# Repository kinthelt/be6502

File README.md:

# be6502
Notes on my Ben Eater 6502 build

## Description

I've been having fun building a 6502 breadboard computer based on Ben Eater's design (https://www.youtube.com/playlist?list=PLowKtXNTBypFbtuVMUVXNR0z1mu7dp7eH)

I made the decision early on to mostly follow along with the videos, but tweak the design a bit so that I would be forced to sit and think rather than just follow a recipe.  One of the major decisions was to use a 65C816S CPU rather than a 65C02S.  The extra 8 bits of address space (called banks) add new problems for me to solve if I am to use them.

On boot, the '816 behaves the same as the '02 as it operates in "emulation mode".  This simplifies things for me as I can treat the build the same as an '02 in bank 00.  If I want to access other banks, I need to store the data line bits in a latch on PHI2 low.  This is the start of where my design differs.

On PHI2 low, I store the data lines in a 74HC573 latch.  This is the bank byte, which I will use later.

The bank byte allows up to 255 banks of 64k each.  A whopping 16MB of address space is available to us.  That being said, I plan on only using a single 512kB RAM chip in my final design.  To start, I will use a single 8kB RAM chip.

With the addition of multiple banks, I won't be able to use a single 7400 to decode addresses without significant shadowing.  So the plan is to use an ATF22V10C programmable logic device to decode addresses.  The PLD allows me to remove some of the "wasted" space in Ben Eater's design.

## Schematic

The KiCad schematic is in [`kicad/`](kicad/), and [`kicad/be6502.pdf`](kicad/be6502.pdf)
is a plot of it. See [`kicad/README.md`](kicad/README.md).

There is also an unfabricated two-layer PCB layout made from the schematic,
[`kicad/be6502.kicad_pcb`](kicad/be6502.kicad_pcb). Renders are in
[`kicad/renders/`](kicad/renders/).

## The Ben Eater Address Space

| Range           | Size    | Device                          | Notes                                      |
|-----------------|---------|---------------------------------|--------------------------------------------|
| `$0000`–`$00FF` | 256 B   | RAM — zero page                 | 62256                                      |
| `$0100`–`$01FF` | 256 B   | RAM — stack                     | 62256                                      |
| `$0200`–`$3FFF` | 15.5 KB | RAM — general                   | 62256 (upper 16 KB of chip unusable)       |
| `$4000`–`$4FFF` | 4 KB    | unmapped                        |                                            |
| `$5000`         | 1 B     | 65C51 ACIA — data register      | read = RX, write = TX                      |
| `$5001`         | 1 B     | 65C51 ACIA — status / reset     | read = status, write = programmed reset    |
| `$5002`         | 1 B     | 65C51 ACIA — command register   |                                            |
| `$5003`         | 1 B     | 65C51 ACIA — control register   |                                            |
| `$5004`–`$5FFF` | ~4 KB   | ACIA register mirrors           | only A0–A1 decoded (RS0–RS1)               |
| `$6000`–`$600F` | 16 B    | 65C22 VIA — 16 registers        | RS0–RS3 = A0–A3                            |
| `$6010`–`$7FFF` | ~8 KB   | VIA register mirrors            | only A0–A3 decoded                         |
| `$8000`–`$FFFF` | 32 KB   | ROM                             | 28C256; vectors at `$FFFA`–`$FFFF`         |

### Address decode

| Device | Select logic |
|--------|--------------|
| ROM    | `/CE = NOT(A15)` |
| RAM    | `/CE = NOT(NOT(A15) AND Φ2)`, `/OE = A14` |
| VIA    | `/CS2 = NOT(NOT(A15) AND A14)`, `CS1 = A13` |
| ACIA   | `/CS1 = NOT(NOT(A15) AND A14 AND NOT(A13) AND A12)`, `CS0 = 1` |

**Quirks:** The 62256 is chip-enabled across `$0000`–`$7FFF`; only `/OE = A14` blocks reads above `$3FFF`. Writes to `$4000`–`$7FFF` still land in the RAM chip and cannot be read back, and writes in `$5000`–`$7FFF` hit RAM and the I/O device simultaneously.

## My Address Space

24-bit address space, notated `bank:offset`.

### Top level

| Range                 | Size   | Contents                                  |
|-----------------------|--------|-------------------------------------------|
| `$00:0000`–`$00:FFFF` | 64 KB  | Bank 0 — RAM, I/O, ROM (see below)        |
| `$01:0000`–`$07:FFFF` | 448 KB | RAM, full banks                           |
| `$08:0000`–`$7F:FFFF` | —      | Aliases of banks `$00`–`$07`              |
| `$80:0000`–`$80:7FFF` | 32 KB  | Video RAM (62256), future, not fitted     |
| `$80:8000`–`$FF:FFFF` | —      | Aliases of `$80:0000`–`$80:7FFF`          |

The GAL already decodes `/VRAMCE` for the video bank, but no video RAM is fitted yet.
GAL pin 17 is unconnected.

RAM total: 472 KB reachable of 512 KB installed (AS6C4008). The 40 KB shortfall is
bank 0's I/O window and ROM window shadowing the SRAM.

### Bank 0

| Range                 | Size    | Contents                                 |
|-----------------------|---------|------------------------------------------|
| `$00:0000`–`$00:00FF` | 256 B   | RAM — direct page (reset default)        |
| `$00:0100`–`$00:01FF` | 256 B   | RAM — stack (reset default)              |
| `$00:0200`–`$00:5FFF` | 23.5 KB | RAM — general                            |
| `$00:6000`–`$00:7FFF` | 8 KB    | I/O window — 74HC138, 8 × 1 KB slots     |
| `$00:8000`–`$00:FFFF` | 32 KB   | ROM (AT28C256)                           |

Direct page and stack are shown at their reset defaults. In native mode both are
relocatable anywhere within bank 0.

### I/O window

74HC138 enabled by `/IO_SELECT` from the GAL, selects driven by A10–A12.

| Output | Range                 | Device       | Registers                          |
|--------|-----------------------|--------------|------------------------------------|
| Y0     | `$00:6000`–`$00:63FF` | W65C22 VIA   | `$6000`–`$600F`, mirrored (A0–A3)  |
| Y1     | `$00:6400`–`$00:67FF` | unallocated  |                                    |
| Y2     | `$00:6800`–`$00:6BFF` | unallocated  |                                    |
| Y3     | `$00:6C00`–`$00:6FFF` | unallocated  |                                    |
| Y4     | `$00:7000`–`$00:73FF` | W65C51N ACIA | `$7000`–`$7003`, mirrored (A0–A1)  |
| Y5     | `$00:7400`–`$00:77FF` | unallocated  |                                    |
| Y6     | `$00:7800`–`$00:7BFF` | unallocated  |                                    |
| Y7     | `$00:7C00`–`$00:7FFF` | unallocated  |                                    |

### Vectors

| Range                 | Mode      |
|-----------------------|-----------|
| `$00:FFE4`–`$00:FFEF` | Native    |
| `$00:FFF8`–`$00:FFFF` | Emulation |

Both sets are in ROM. ROM is fixed at `$00:8000` — no vector remap or bank switching.

### Decode

Bank byte A16–A23 is captured from D0–D7 by a 74HC573, LE driven by `/PHI2`.

GAL (ATF22V10C) inputs: A12–A15, A16–A18, A23, PHI2, RWB.
A19–A22 are deliberately left as don't-cares — hence the aliasing above. Tighten
this first if a second RAM or VRAM device is ever added.

A16–A18 feed the SRAM address pins directly; the GAL uses them only to identify
bank 0. A23 alone separates the RAM banks from the video bank.

`/WE_RAM` is gated `PHI2 AND /RWB`. Raw RWB would write during PHI2 low, when the
data bus still carries the bank byte.

# Pinout Reference — 75HC138 and W65C22

For the 65C816 breadboard build. I/O window `$00:6000–$00:7FFF`,
enabled by IOSEL from the ATF22V10C (816DEC01).

---

## 74HC138 — 3-to-8 Line Decoder, DIP-16

| Pin | Name | Connect to |
|----:|------|------------|
| 1 | A | A10 |
| 2 | B | A11 |
| 3 | C | A12 |
| 4 | /E1 (/G2A) | IOSEL, GAL pin 20 |
| 5 | /E2 (/G2B) | GND — reserved PHI2 hook |
| 6 | E3 (G1) | VCC |
| 7 | Y7 | $7C00 slot |
| 8 | GND | GND |
| 9 | Y6 | $7800 slot |
| 10 | Y5 | $7400 slot |
| 11 | Y4 | $7000 — ACIA |
| 12 | Y3 | $6C00 slot |
| 13 | Y2 | $6800 slot |
| 14 | Y1 | $6400 slot |
| 15 | Y0 | $6000 — VIA CS2B |
| 16 | VCC | +5V |

100 nF from pin 16 to pin 8, close to the package, is the usual
recommendation. This build has no per-chip decoupling (no room). The
only decoupling capacitor is a 0.1 µF electrolytic across +5V and GND
at the bench supply connection.

### Output behaviour

All eight outputs idle **high**. Exactly one goes low at a time, and
only when every enable is satisfied. Nothing is selected at rest.

| Condition | Outputs |
|-----------|---------|
| Any enable unsatisfied | all eight high |
| Enabled, CBA = 000 | Y0 low, rest high |
| Enabled, CBA = 100 | Y4 low, rest high |

### Enables

Mixed polarity. All three must be true at once:

- pin 4 — LOW
- pin 5 — LOW
- pin 6 — HIGH

Naming varies by manufacturer. TI uses /G2A, /G2B, G1; others use
/E1, /E2, E3. Same pins, same behaviour, different letters. A
schematic found online may not match the datasheet in hand.

Pin 6 is the trap — the only active-high enable, sitting next to the
two active-low ones. Tied low, the part has no outputs at all and no
obvious reason why.

### Slot mapping

C:B:A = A12:A11:A10, straight through.

| Output | Address range | Device |
|--------|---------------|--------|
| Y0 | $00:6000–$00:63FF | W65C22 VIA |
| Y1 | $00:6400–$00:67FF | unallocated |
| Y2 | $00:6800–$00:6BFF | unallocated |
| Y3 | $00:6C00–$00:6FFF | unallocated |
| Y4 | $00:7000–$00:73FF | W65C51N ACIA |
| Y5 | $00:7400–$00:77FF | unallocated |
| Y6 | $00:7800–$00:7BFF | unallocated |
| Y7 | $00:7C00–$00:7FFF | unallocated |

Unused outputs are totem-pole, not open-drain — nothing to pull.
Leave open, or run to a header row while breadboarding.

---

## W65C22 VIA — DIP-40

| Pin | Signal | Connect to |
|----:|--------|------------|
| 1 | VSS | GND |
| 2–9 | PA0–PA7 | peripheral, ascending |
| 10–17 | PB0–PB7 | peripheral, ascending |
| 18 | CB1 | peripheral / shift clock |
| 19 | CB2 | peripheral / serial data |
| 20 | VDD | +5V |
| 21 | IRQB | CPU IRQB — see note |
| 22 | RWB | CPU RWB |
| 23 | CS2B | 74HC138 Y0, pin 15 |
| 24 | CS1 | VCC |
| 25 | PHI2 | system PHI2 |
| 26–33 | D7–D0 | data bus, **descending** |
| 34 | RESB | system reset |
| 35–38 | RS3–RS0 | A3–A0, **descending** |
| 39 | CA2 | peripheral |
| 40 | CA1 | peripheral |

### Chip select

To access a register: CS1 = logic 1 AND CS2B = logic 0.

CS1 is the tie-high enable, not the main select. WDC's default for
unused pins says the same thing from the other side — hold CS1 high,
hold CS2B low.

Y0 is active low, so it must land on CS2B. Y0 on CS1 selects the chip
whenever the slot is *not* addressed, and the VIA fights RAM and ROM
on the data bus every cycle.

### Descending pin runs

Pin 26 = D7, pin 33 = D0.
Pin 35 = RS3, pin 38 = RS0.

Both numbered opposite to the PA and PB runs on the same package.
Reversing the data bus produces bit-mirrored reads and writes that
look like a dead chip.

### IRQB — check the part marking

| Variant | IRQB output | Wiring |
|---------|-------------|--------|
| W65C22N, older NMOS/CMOS | open drain, pull down only | wire-OR, one pullup on the common line |
| W65C22S | totem pole, drives both levels | logic OR gate, or a <0.5 V diode in series, forward biased when IRQB is low, plus a pullup |

The W65C22S IRQB was meant for logically ORing rather than wire ORing.
Tying an S variant directly to another driven IRQ line is a driver
fight.

With the ACIA on the same node, this decides the interrupt topology
for the whole system. Settle it before wiring either chip.

This build uses a **W65C22N6TPG-14** (open drain). Its IRQB is wired
directly to the shared IRQB line with the ACIA, with a single pull-up
and no diode.

### Processor interface timing — 5 V, 14 MHz

| Symbol | Parameter | Min |
|--------|-----------|-----|
| tACR / tACW | CSx, RSx, RWB setup | 10 ns |
| tCAR / tCAW | CSx, RSx, RWB hold from PHI2 rising | 10 ns |
| tDCW | data bus setup (write) | 10 ns |
| tCDR | data bus delay (read) | 20 ns max |

The 10 ns setup is what the decode chain must beat:

    74HC573 → ATF22V10C → 74HC138 → CS2B

all settled 10 ns before PHI2 rises.

### W65C22S-specific

- **No output current limiting.** The S variant can overdrive
  connected circuitry. The NMOS 6522 and W65C22N have series
  resistors built in. Add external resistors on PA/PB when driving
  LEDs or an HD44780.
- **Bus holding on every pin except PHI2.** A floating input holds
  its last state rather than drifting — so a disconnected jumper can
  look like a working connection until something changes it.

---

## Signal chain

Active low end to end:

    IOSEL low  →  '138 enabled  →  one Y low  →  CS2B low  →  VIA selected

No inverters anywhere in the path.

---

## Sources

- WDC W65C22 datasheet (W65C22N and W65C22S), Sept 13 2010
- Standard 6522 DIP-40 pin numbering, which the W65C22 follows

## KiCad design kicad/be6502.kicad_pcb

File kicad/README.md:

# KiCad schematic and PCB

Schematic for the W65C816S breadboard computer, as built, and a two-layer PCB
laid out from it. Open `be6502.kicad_pro` in KiCad 7 or newer. `be6502.pdf` is
a plot of all sheets.

## Sheets

| Sheet | Contents |
|-------|----------|
| `be6502.kicad_sch` | Root: sheet index, memory map |
| `cpu.kicad_sch` | U1 W65C816S, U2 74HC573 bank latch, U3 ATF22V10C (816DEC02), X1 12 MHz oscillator, reset |
| `memory.kicad_sch` | U4 AT28C256 ROM, U5 AS6C4008 RAM |
| `io.kicad_sch` | U6 74HC138, U7 W65C22N VIA with Port B LEDs, U8 W65C51N ACIA, X2 1.8432 MHz oscillator, U9 MAX232N, J2 DB9 |
| `power.kicad_sch` | J1 bench supply, C1 |

Sheets connect through global labels.

## Signal names

Active-low signals use KiCad's overbar notation in both net labels and pin
names: `~{IOSEL}`, `~{ROMCE}`, `~{RAMCE}`, `~{OEGATE}`, `~{WEGATE}`, `~{RES}`,
`~{IRQ}`, `R/~{W}`, and so on.

| Schematic | decode.pld | WDC datasheet |
|-----------|------------|---------------|
| `~{IOSEL}` | `/IOSEL` | — |
| `R/~{W}` | `RWB` | RWB |
| `~{RES}` | — | RESB |
| `~{IRQ}` | — | IRQB |
| `~{CS2}` (VIA) | — | CS2B |
| `~{CS1}` (ACIA) | — | CS1B |

KiCad stores `/` in a net name as `{slash}`, so the read/write net is
`R{slash}~{W}` in the files. It still displays as R/W with a bar over the W.

The project library `be6502.kicad_sym` contains every symbol the schematic
uses. The W65C816S, W65C22, W65C51N and the programmed ATF22V10C are drawn
from the WDC and Microchip pinouts. The other parts are copied from the stock
KiCad libraries, with pins such as `OE`, `Load` and `CE#` renamed to `~{OE}`,
`LE` and `~{CE}`.

## Wiring

**CPU (U1)**
- `~{ABORT}`, BE, RDY and `~{NMI}` are tied directly to +5V.
- VDA, VPA, `~{VP}`, `~{ML}`, E and MX are not connected.
- `~{RES}` has a pull-up (R1) and a push button (SW1) to GND.
- `~{IRQ}` has a pull-up (R2). It is shared by the VIA and the ACIA, both open drain, with no diode.

**Clock**
- X1 is a 12 MHz DIP-14 oscillator driving GAL pin 1 (CLK2). The GAL divides it to PHI2 = 6 MHz.
- X1 pin 1 is not connected.

**Bank latch and decode (U2, U3)**
- The GAL pins are exactly as in the `PIN ASSIGNMENT` section of `pld/decode.pld`.
- `~{VRAMCE}` (GAL pin 17) is not connected, because the video RAM is future expansion.
- GAL pins 11, 13, 15 and 16 are spare.
- On the 74HC573, `~{OE}` goes to GND and LE comes from GAL pin 14.
- Q0–Q2 drive A16–A18 and Q7 drives A23. Q3–Q6 are not connected.

**Memory (U4, U5)**
- The ROM and RAM share `~{OEGATE}`.
- `~{WEGATE}` goes only to the RAM's `~{WE}`. The ROM's `~{WE}` is tied high.

**I/O decoder (U6, 74HC138)**
- A/B/C = A10/A11/A12.
- `~{E0}` = `~{IOSEL}`, `~{E1}` = GND, E2 = +5V.
- Y0 goes to the VIA's `~{CS2}` and Y4 to the ACIA's `~{CS1}`. The other outputs are not connected.

**VIA (U7, W65C22N6TPG-14)**
- CS1 = +5V, RS0–RS3 = A0–A3.
- Port A, CA1, CA2, CB1 and CB2 are not connected.
- Each PBn drives an LED (D1–D8) and a resistor (R3–R10) to GND: PBn → LED → resistor → GND.

**ACIA (U8)**
- CS0 = +5V, RS0–RS1 = A0–A1.
- X2 is a 1.8432 MHz DIP-8 oscillator driving XTLI. X2 pin 1 (EN) is tied to +5V.
- XTLO, RxC and `~{DTR}` are not connected. `~{CTS}`, `~{DSR}` and `~{DCD}` are tied to GND.

**RS-232 (U9 MAX232N, J2 DB9 female)**
- ACIA TxD → T1IN → T1OUT → DB9 pin 2.
- DB9 pin 3 → R1IN → R1OUT → ACIA RxD.
- ACIA `~{RTS}` → T2IN → T2OUT → DB9 pin 8.
- DB9 pin 5 = GND. DB9 pins 1, 4, 6, 7 and 9 are not connected.
- R2IN and R2OUT are not connected.
- The charge-pump capacitors are 1 µF electrolytics: C2 across C1+/C1−, C3 across C2+/C2−, C4 from VS+ to GND, C5 from VS− to GND.

**Power**
- J1 represents the leads from the +5V bench supply.
- C1 (0.1 µF electrolytic) across +5V and GND at the supply connection is the only decoupling capacitor.

**Resistor values**
- R1–R10 are 1k, measured with a multimeter.

## PCB

`be6502.kicad_pcb` is a 175 × 125 mm two-layer, all through-hole board made
from the schematic. It shows what the computer would look like on a PCB. It
has not been fabricated.

- Bare-board renders: `renders/front.png` and `renders/back.png`.
- 0.2 mm signal tracks and 0.5 mm `VCC`/`GND` tracks (net class `Power`),
  0.2 mm clearance, 0.8/0.4 mm vias. Both layers have a `GND` pour.
- Footprints the schematic did not specify: R 0207 axial with 7.62 mm pitch,
  C 5 mm radial electrolytic, 3 mm LEDs, 6 mm tactile switch for SW1, a 2-pin
  5.08 mm screw terminal for J1 (bench supply), and a right-angle female DE-9
  for J2.
- H1–H4 are M3 mounting holes. They exist only on the board.
- The tracks came from a simple
  grid router in `pcb-tools/` (`build.py` places, `route.py` routes,
  `finish.py` pours and writes the DRC report, `compose.py` and `render.js`
  make the images).
- DRC with KiCad 7.0.11 reports 0 violations and 0 unconnected pads.

The board follows the schematic exactly, so C1 is the only decoupling
capacitor. A real board should have a 0.1 µF capacitor next to each chip's
power pins. Add them to the schematic first, then use *Update PCB from
Schematic*.

## Verification

The project was generated with KiCad 7.0 and checked with `kicad-cli sch
export netlist`. Every net matches the wiring above, and the only unconnected
pins are the ones marked no-connect. ERC has not been run, because
`kicad-cli` 7 has no ERC command. Run it in the GUI.

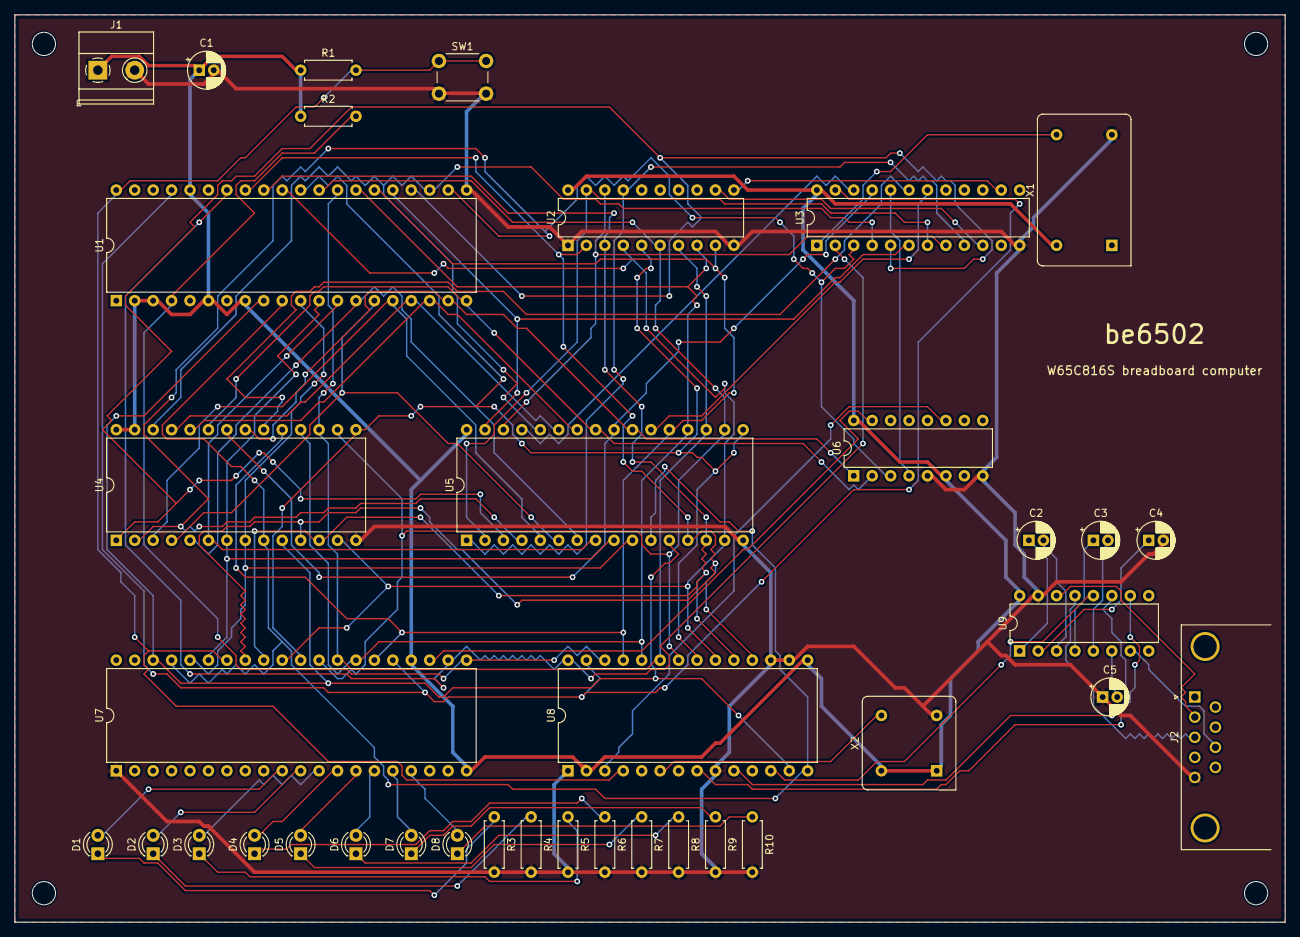
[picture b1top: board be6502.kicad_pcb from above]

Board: 2 copper layers, 175.0 x 125.0 mm, 41 parts (0 on the bottom side), 72 nets.

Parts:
C1: 0.1uF; CP_Radial_D5.0mm_P2.00mm
C2, C3, C4, C5: 1uF; CP_Radial_D5.0mm_P2.00mm
D1, D2, D3, D4, D5, D6, D7, D8: LED; LED_D3.0mm
H1, H2, H3, H4: MountingHole_3.2mm_M3
J1: BENCH SUPPLY +5V; TerminalBlock_Phoenix_MKDS-1,5-2-5.08_1x02_P5.08mm_Horizont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
J2: DB9 female; DSUB-9_Female_Horizontal_P2.77x2.84mm_EdgePinOffset7.70mm_H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
R1, R2, R3, R4, R5, R6, R7, R8, R9, R10: 1k; R_Axial_DIN0207_L6.3mm_D2.5mm_P7.62mm_Horizontal
SW1: RESET; SW_PUSH_6mm
U1: W65C816S; DIP-40_W15.24mm
U2: 74HC573; DIP-20_W7.62mm
U3: ATF22V10C 816DEC02; DIP-24_W7.62mm
U4: AT28C256; DIP-28_W15.24mm
U5: AS6C4008; DIP-32_W15.24mm
U6: 74HC138; DIP-16_W7.62mm
U7: W65C22N6TPG-14; DIP-40_W15.24mm
U8: W65C51N; DIP-28_W15.24mm
U9: MAX232N; DIP-16_W7.62mm
X1: 12MHz; Oscillator_DIP-14
X2: 1.8432MHz; Oscillator_DIP-8

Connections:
A0: U1.9, U4.10, U5.12, U7.38, U8.13
A1: U1.10, U4.9, U5.11, U7.37, U8.14
A2: U1.11, U4.8, U5.10, U7.36
A3: U1.12, U4.7, U5.9, U7.35
A4: U1.13, U4.6, U5.8
A5: U1.14, U4.5, U5.7
A6: U1.15, U4.4, U5.6
A7: U1.16, U4.3, U5.5
A8: U1.17, U4.25, U5.27
A9: U1.18, U4.24, U5.26
A10: U1.19, U4.21, U5.23, U6.1
A11: U1.20, U4.23, U5.25, U6.2
A12: U1.22, U3.3, U4.2, U5.4, U6.3
A13: U1.23, U3.4, U4.26, U5.28
A14: U1.24, U3.5, U4.1, U5.3
A15: U1.25, U3.6, U5.31
A16: U2.19, U3.7, U5.2
A17: U2.18, U3.8, U5.30
A18: U2.17, U3.9, U5.1
A23: U2.12, U3.10
ACIA_CLK: U8.6, X2.5
ACIA_RXD: U8.12, U9.12
ACIA_TXD: U8.10, U9.11
CLK2: U3.1, X1.8
D0: U1.33, U2.2, U4.11, U5.13, U7.33, U8.18
D1: U1.32, U2.3, U4.12, U5.14, U7.32, U8.19
D2: U1.31, U2.4, U4.13, U5.15, U7.31, U8.20
D3: U1.30, U2.5, U4.15, U5.17, U7.30, U8.21
D4: U1.29, U2.6, U4.16, U5.18, U7.29, U8.22
D5: U1.28, U2.7, U4.17, U5.19, U7.28, U8.23
D6: U1.27, U2.8, U4.18, U5.20, U7.27, U8.24
D7: U1.26, U2.9, U4.19, U5.21, U7.26, U8.25
GND: C1.2, C4.2, C5.1, J1.2, J2.5, R3.2, R4.2, R5.2, R6.2, R7.2, R8.2, R9.2, R10.2, SW1.2, U1.21, U2.1, U2.10, U3.12, U4.14, U5.16, U6.5, U6.8, U7.1, U8.1, U8.9, U8.16, U8.17, U9.15, X1.7, X2.4
LE: U2.11, U3.14
MAX232_VS+: C4.1, U9.2
MAX232_VS-: C5.2, U9.6
unnamed: D1.1, R3.1
unnamed: D2.1, R4.1
unnamed: D3.1, R5.1
unnamed: D4.1, R6.1
unnamed: D5.1, R7.1
unnamed: D6.1, R8.1
unnamed: D7.1, R9.1
unnamed: D8.1, R10.1
unnamed: C2.1, U9.1
unnamed: C2.2, U9.3
unnamed: C3.1, U9.4
unnamed: C3.2, U9.5
PB0: D1.2, U7.10
PB1: D2.2, U7.11
PB2: D3.2, U7.12
PB3: D4.2, U7.13
PB4: D5.2, U7.14
PB5: D6.2, U7.15
PB6: D7.2, U7.16
PB7: D8.2, U7.17
PHI2: U1.37, U3.23, U7.25, U8.27
RS232_RTS: J2.8, U9.7
RS232_RXD: J2.3, U9.13
RS232_TXD: J2.2, U9.14
R/~W: U1.34, U3.2, U7.22, U8.28
VCC: C1.1, J1.1, R1.1, R2.1, U1.2, U1.3, U1.6, U1.8, U1.36, U2.20, U3.24, U4.27, U4.28, U5.32, U6.6, U6.16, U7.20, U7.24, U8.2, U8.15, U9.16, X1.14, X2.1, X2.8
~ACIA_CS: U6.11, U8.3
~ACIA_RTS: U8.8, U9.10
~IOSEL: U3.20, U6.4
~IRQ: R2.2, U1.4, U7.21, U8.26
~OEGATE: U3.21, U4.22, U5.24
~RAMCE: U3.18, U5.22
~RES: R1.2, SW1.1, U1.40, U7.34, U8.4
~ROMCE: U3.19, U4.20
~VIA_CS: U6.15, U7.23
~WEGATE: U3.22, U5.29
